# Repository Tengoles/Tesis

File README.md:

# Tesis
Tesis de grado - Enzo Pacilio Pablo Alonso

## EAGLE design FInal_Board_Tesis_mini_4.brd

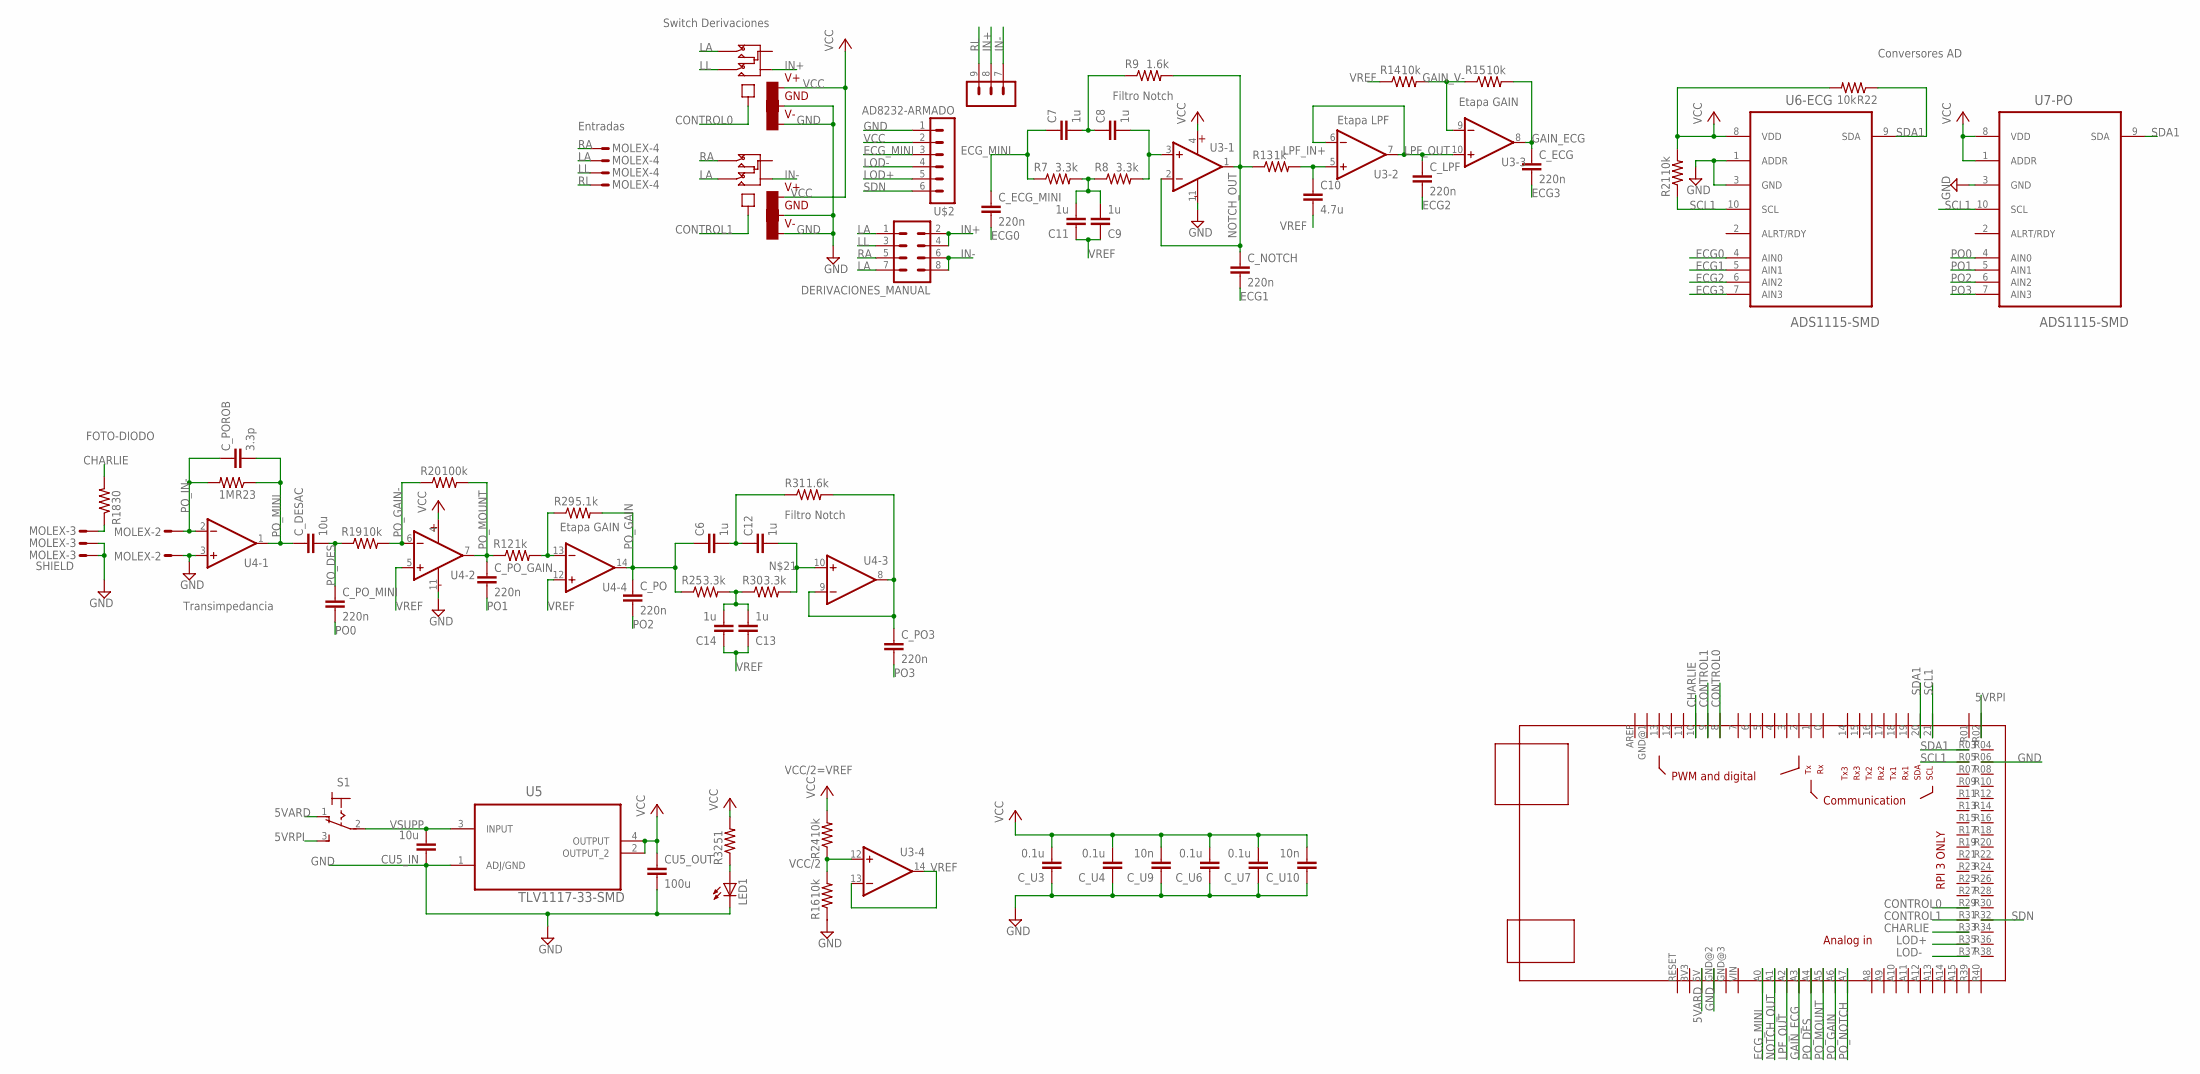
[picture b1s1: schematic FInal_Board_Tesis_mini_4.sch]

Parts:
C6, C7, C8, C9, C11, C12, C13, C14: 1u; C0805
C10: 4.7u; C0805
CU5_IN: 10u; C0805
CU5_OUT: 100u; C0805
C_DESAC: 10u; C0805
C_ECG: 220n; C0805
C_ECG_MINI: 220n; C0805
C_LPF: 220n; C0805
C_NOTCH: 220n; C0805
C_PO, C_PO3: 220n; C0805
C_POROB: 3.3p; C0805
C_PO_GAIN: 220n; C0805
C_PO_MINI: 220n; C0805
C_U3, C_U4, C_U6, C_U7: 0.1u; C0805
C_U9, C_U10: 10n; C0805
DERIVACIONES_MANUAL: MA04-2
LED1: LED_E; LED_1206
R7, R8, R25, R30: 3.3k; M3216
R9, R31: 1.6k; M3216
R12, R13: 1k; M3216
R14, R15, R16, R19, R21, R22, R24: 10k; M3216
R18: 30; M3216
R20: 100k; M3216
R23: 1M; M3216
R29: 5.1k; M3216
R32: 51; M3216
S1: 320-916
U3, U4: OPA4348-SMD; 14TSSOP
U5: TLV1117-33-SMD; SOT223
U6-ECG, U7-PO: ADS1115-SMD; 10MSOP
U9, U10: MAX4528-SMD; 8MSOP-C/PTO
U$1: MEGA_DEVICE; MEGABOX
U$2: AD8232-ARMADO; PINES-ECG
U$3: MOLEX-3
U$4: MOLEX-2
U$5: MOLEX-4

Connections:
5VARD: S1.1 (O), U$1.5V
5VRPI: S1.3 (S), U$1.R02 (5V1)
CHARLIE: R18.2, U$1.10, U$1.R33 (GPIO13)
CONTROL0: U9.4 (IN), U$1.8, U$1.R29 (GPIO5)
CONTROL1: U10.4 (IN), U$1.9, U$1.R31 (GPIO6)
ECG0: C_ECG_MINI.2, U6-ECG.4 (AIN0)
ECG1: C_NOTCH.2, U6-ECG.5 (AIN1)
ECG2: C_LPF.2, U6-ECG.6 (AIN2)
ECG3: C_ECG.2, U6-ECG.7 (AIN3)
ECG_MINI: C7.1, C_ECG_MINI.1, R7.1, U$1.A0, U$2.3 (OUT)
GAIN_ECG: C_ECG.1, R15.2, U3.8 (OUT), U$1.A3
GAIN_V-: R14.2, R15.1, U3.9 (-IN)
GND: CU5_IN.1, CU5_OUT.2, C_U3.1, C_U4.1, C_U6.1, C_U7.1, C_U9.1, C_U10.1, LED1.C, R16.1, U3.11 (V-), U4.3 (+IN), U4.11 (V-), U5.1 (ADJ/GND), U6-ECG.1 (ADDR), U6-ECG.3 (GND), U7-PO.3 (GND), U9.3 (GND), U9.5 (V-), U10.3 (GND), U10.5 (V-), U$1.GND@2 (GND), U$1.R06 (GND), U$2.1 (GND), U$3.2, U$3.3, U$4.2
IN+: DERIVACIONES_MANUAL.2, DERIVACIONES_MANUAL.4, U9.6 (Y), U$2.8 (LA)
IN-: DERIVACIONES_MANUAL.6, DERIVACIONES_MANUAL.8, U10.6 (Y), U$2.7 (RA)
LA: DERIVACIONES_MANUAL.1, DERIVACIONES_MANUAL.7, U9.1 (A), U10.2 (B), U$5.2
LL: DERIVACIONES_MANUAL.3, U9.2 (B), U$5.3
LOD+: U$1.R35 (GPIO19), U$2.5 (LOD+)
LOD-: U$1.R37 (GPIO26), U$2.4 (LOD-)
LPF_IN+: C10.1, R13.2, U3.5 (+IN)
LPF_OUT: C_LPF.1, U3.6 (-IN), U3.7 (OUT), U3.10 (+IN), U$1.A2
unnamed: C6.2, C12.1, R31.1
unnamed: C7.2, C8.1, R9.1
unnamed: C8.2, R8.2, U3.3 (+IN)
unnamed: C9.2, C11.2, R7.2, R8.1
unnamed: R18.1, U$3.1
unnamed: C13.2, C14.2, R25.2, R30.1
unnamed: R12.2, R29.1, U4.13 (-IN)
unnamed: LED1.A, R32.1
unnamed: C12.2, R30.2, U4.10 (+IN)
NOTCH_OUT: C_NOTCH.1, R9.2, R13.1, U3.1 (OUT), U3.2 (-IN), U$1.A1
PO0: C_PO_MINI.2, U7-PO.4 (AIN0)
PO1: C_PO_GAIN.2, U7-PO.5 (AIN1)
PO2: C_PO.2, U7-PO.6 (AIN2)
PO3: C_PO3.2, U7-PO.7 (AIN3)
PO_DES: C_DESAC.2, C_PO_MINI.1, R19.1, U$1.A4
PO_GAIN: C6.1, C_PO.1, R25.1, R29.2, U4.14 (OUT), U$1.A6
PO_GAIN-: R19.2, R20.1, U4.6 (-IN)
PO_IN-: C_POROB.1, R23.2, U4.2 (-IN), U$4.1
PO_MINI: C_DESAC.1, C_POROB.2, R23.1, U4.1 (OUT)
PO_MOUNT: C_PO_GAIN.1, R12.1, R20.2, U4.7 (OUT), U$1.A5
PO_NOTCH: C_PO3.1, R31.2, U4.8 (OUT), U4.9 (-IN), U$1.A7
RA: DERIVACIONES_MANUAL.5, U10.1 (A), U$5.1
RL: U$2.9 (RL), U$5.4
SCL1: R21.1, U6-ECG.10 (SCL), U7-PO.10 (SCL), U$1.21, U$1.R05 (SCL1)
SDA1: R22.1, U6-ECG.9 (SDA), U7-PO.9 (SDA), U$1.20, U$1.R03 (SDA1)
SDN: U$1.R32 (GPIO12), U$2.6 (!SDN)
VCC: CU5_OUT.1, C_U3.2, C_U4.2, C_U6.2, C_U7.2, C_U9.2, C_U10.2, R21.2, R22.2, R24.2, R32.2, U3.4 (V+), U4.4 (V+), U5.2 (OUTPUT_2), U5.4 (OUTPUT), U6-ECG.8 (VDD), U7-PO.1 (ADDR), U7-PO.8 (VDD), U9.8 (V+), U10.8 (V+), U$2.2 (3.3V)
VCC/2: R16.2, R24.1, U3.12 (+IN)
VREF: C9.1, C10.2, C11.1, C13.1, C14.1, R14.1, U3.13 (-IN), U3.14 (OUT), U4.5 (+IN), U4.12 (+IN)
VSUPP: CU5_IN.2, S1.2, U5.3 (INPUT)

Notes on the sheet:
Filtro Notch
Etapa LPF
VCC/2=VREF
Etapa GAIN
FOTO-DIODO
Switch Derivaciones
Entradas
Conversores AD
SHIELD
Transimpedancia

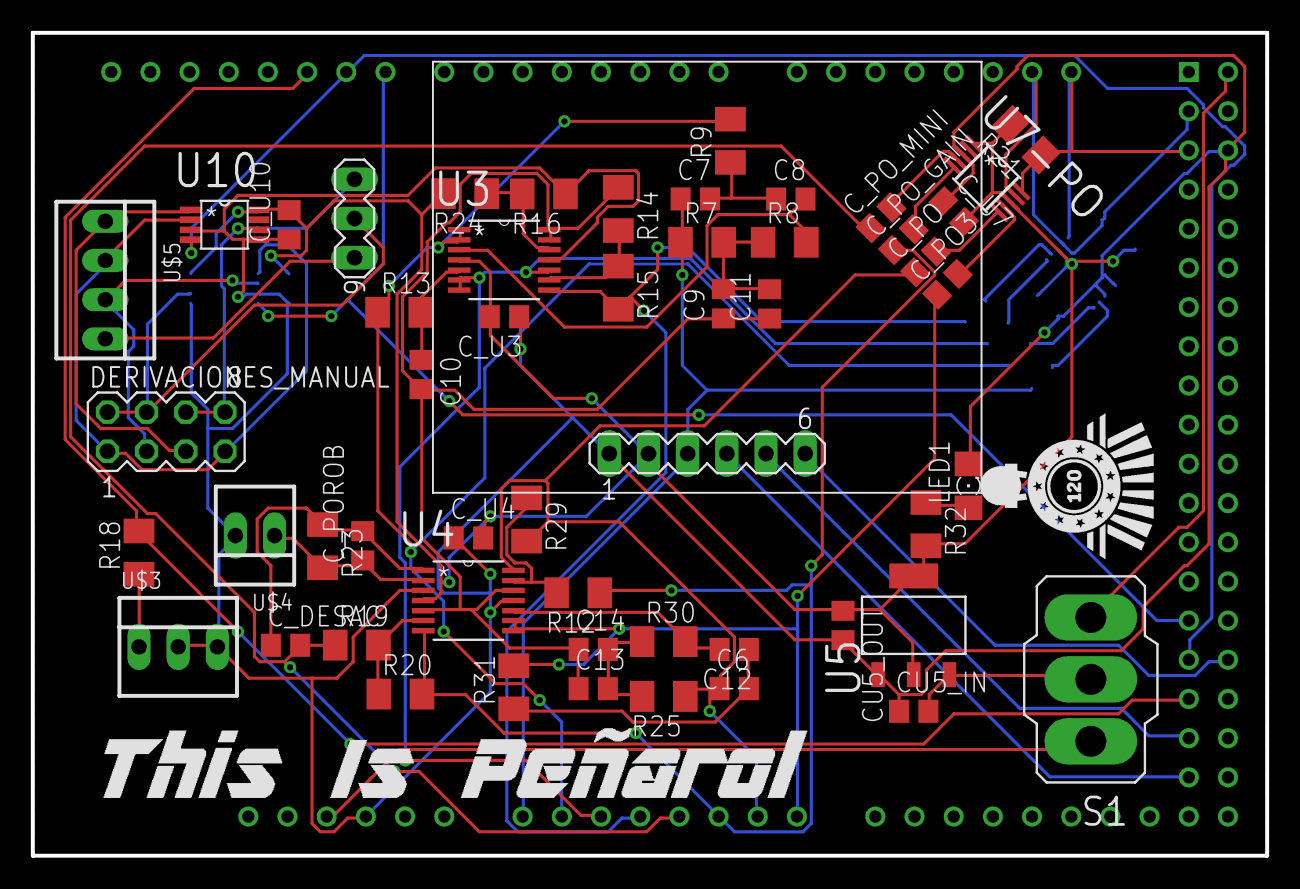
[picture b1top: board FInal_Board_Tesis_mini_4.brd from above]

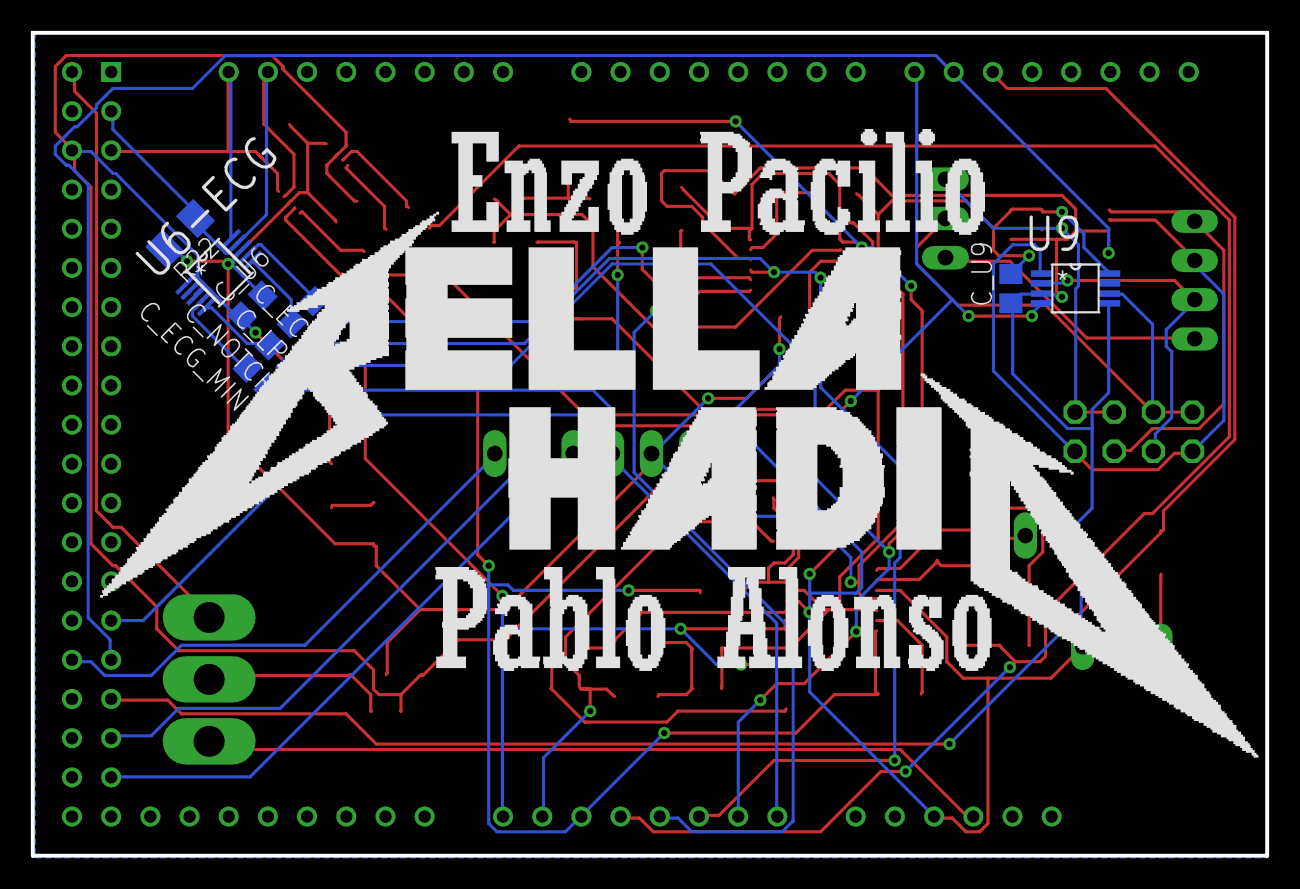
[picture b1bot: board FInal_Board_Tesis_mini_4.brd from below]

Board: 2 copper layers, 80.0 x 53.3 mm, 62 parts (9 on the bottom side), 51 nets.

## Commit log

2018-01-16 primer muestreo
2018-01-16 tiempo en eje X
2018-01-16 agregar filtrado y cambios en muestreo
2018-01-16 filtrado digital
2018-01-16 promedio de samples
2018-01-16 nueva forma de leer adc
2018-03-15 agregar double y cambios simple
2018-03-15 agregar funcion de filtrado
2018-03-25 Modulo adaptado para controlar el ADC
2018-03-26 pila de mierda
2018-03-26 cambios
2018-04-18 Dejarlo rico
2018-04-18 mejoras, todo anda re bien
2018-04-26 archivo con datos de Enzo para pruebas
2018-04-26 cambio de nombre a la libreria principal
2018-04-26 version mejorada de adc
2018-05-02 prueba de filtros
2018-09-28 graficar PO sin filtrar y leer canal 2 del ECG
2018-10-18 borrar estas mierdas
2018-10-28 agregar este script, es casi lo mismo que adc2 pero con GUI y guardado de datos en csv
2018-10-31 Archivos del esquematico y board en Eagle
    Archivos del esquematico y board en Eagle
2018-12-19 Processing files 4 Arduino Mega
    lml
